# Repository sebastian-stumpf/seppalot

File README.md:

# seppalot
4x3 macropad with 3 rotary encoders

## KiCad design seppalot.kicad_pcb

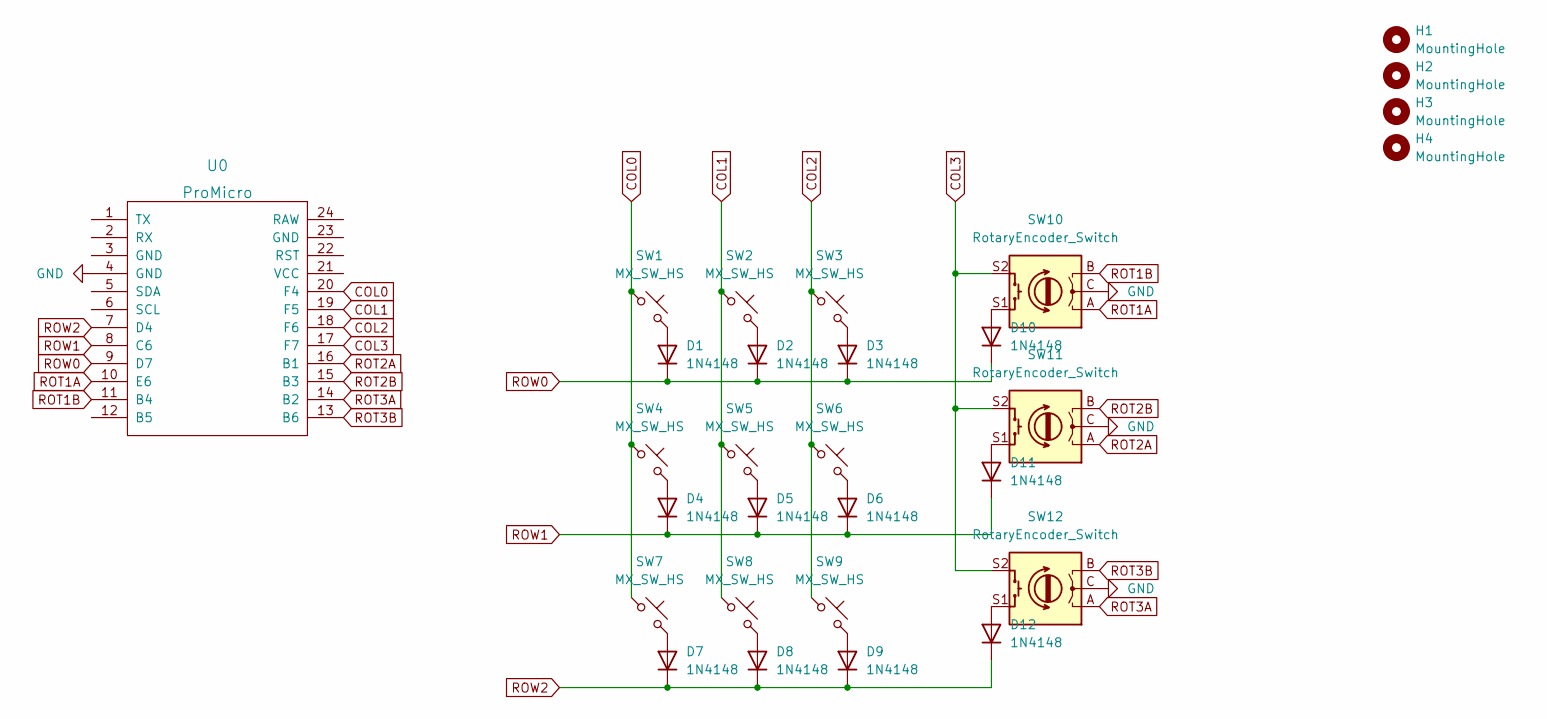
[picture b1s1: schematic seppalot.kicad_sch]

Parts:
D1, D2, D3, D4, D5, D6, D7, D8, D9, D10, D11, D12: 1N4148; D_DO-35_SOD27_P7.62mm_Horizontal
H1, H2, H3, H4: MountingHole; MountingHole_2.2mm_M2_DIN965
SW1, SW2, SW3, SW4, SW5, SW6, SW7, SW8, SW9: MX_SW_HS; SW_MX_HS_1u
SW10, SW11, SW12: RotaryEncoder_Switch; ROT_Alps_EC11E-Switch
U0: ProMicro

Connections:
COL0: SW1.1, SW4.1, SW7.1, U0.20 (F4)
COL1: SW2.1, SW5.1, SW8.1, U0.19 (F5)
COL2: SW3.1, SW6.1, SW9.1, U0.18 (F6)
COL3: SW10.S2, SW11.S2, SW12.S2, U0.17 (F7)
GND: SW10.C, SW11.C, SW12.C, U0.4 (GND)
unnamed: D1.2 (A), SW1.2
unnamed: D2.2 (A), SW2.2
unnamed: D3.2 (A), SW3.2
unnamed: D4.2 (A), SW4.2
unnamed: D5.2 (A), SW5.2
unnamed: D6.2 (A), SW6.2
unnamed: D7.2 (A), SW7.2
unnamed: D8.2 (A), SW8.2
unnamed: D9.2 (A), SW9.2
unnamed: D10.2 (A), SW10.S1
unnamed: D11.2 (A), SW11.S1
unnamed: D12.2 (A), SW12.S1
ROT1A: SW10.A, U0.10 (E6)
ROT1B: SW10.B, U0.11 (B4)
ROT2A: SW11.A, U0.16 (B1)
ROT2B: SW11.B, U0.15 (B3)
ROT3A: SW12.A, U0.14 (B2)
ROT3B: SW12.B, U0.13 (B6)
ROW0: D1.1 (K), D2.1 (K), D3.1 (K), D10.1 (K), U0.9 (D7)
ROW1: D4.1 (K), D5.1 (K), D6.1 (K), D11.1 (K), U0.8 (C6)
ROW2: D7.1 (K), D8.1 (K), D9.1 (K), D12.1 (K), U0.7 (D4)

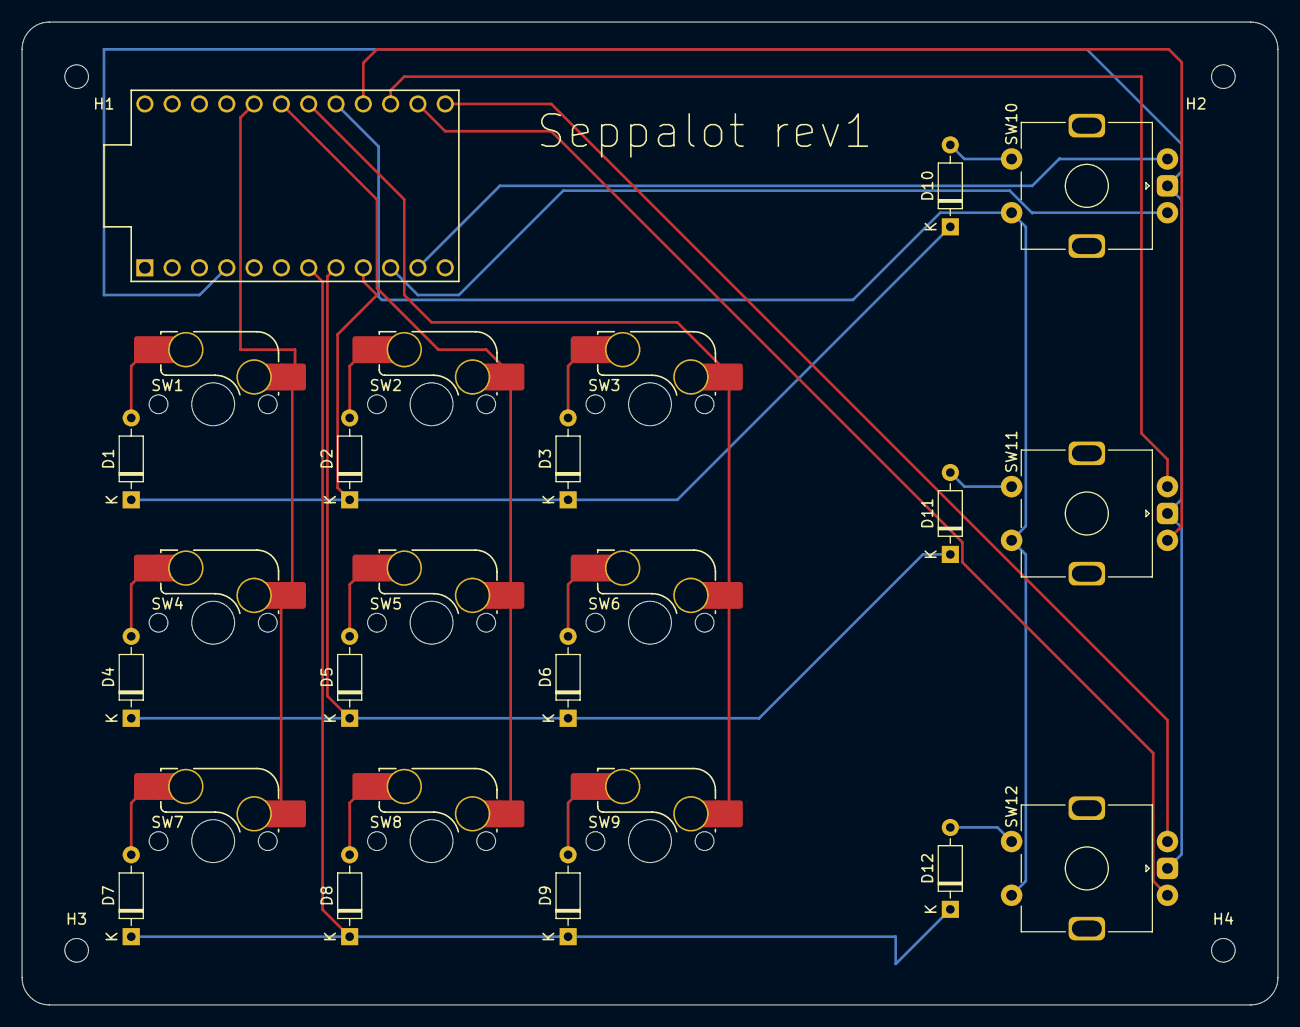
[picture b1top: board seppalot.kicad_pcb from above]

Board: 2 copper layers, 116.8 x 91.4 mm, 29 parts (0 on the bottom side), 26 nets.

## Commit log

2023-01-28 initial import
